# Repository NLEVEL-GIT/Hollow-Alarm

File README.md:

# HollowAlarm

    HollowAlarm was my ship for the Blare Mission of Stardance Hackclub
    HollowAlarm features a simple clock like shape design with 4 keys to control

# Features:

    - 2.25 Inch TFT Display
    - 4 Keys
    - Buzzer... cuz its and alarm

# CAD Model:

    HollowPad is divided in 4 parts.
    - the main shell where eveything connects that include a sorta of cabinet design and dovetail joints to connect to the shell of the alarm.
    - The shell itself consisting of the front piece and back piece to close the clock design

    Everything was in Fusion cuz its lowk fire

# PCB
    It was made in KiCad. Only requiring extra footprints ansd symbols provided by the Blare page!

    The footprints for the Switches are standart MX style Switches!

**Schematic:**

**PCB Layout:**

    Also it has a lot of small silkscreens cuz they lowk cool!

# Firmware Overview
    The firmware can be described as spaghetti code secured by hopes and dreams.
    It gives each button its own function and has a way to swap between 4 background which I made! More can be added by changing the background.h file on the firmware

# BOM:
    Here should be everything you need to make this hackpad

    - 4x Cherry MX Switches
    - 4x DSA Keycaps (or you can make some if u want)
    - 1x Buzzer
    - 1x 2.25" 284x76 TFT Display
    - 1x XIAO ESP32C3
    - 1x Case (4 Printed Parts)

# Extra stuff
    To anyone that is reading the end of this READ ME i wana say thanks for atleast checking out my project.
    With that thanks again and Good Luck on your projects!!!

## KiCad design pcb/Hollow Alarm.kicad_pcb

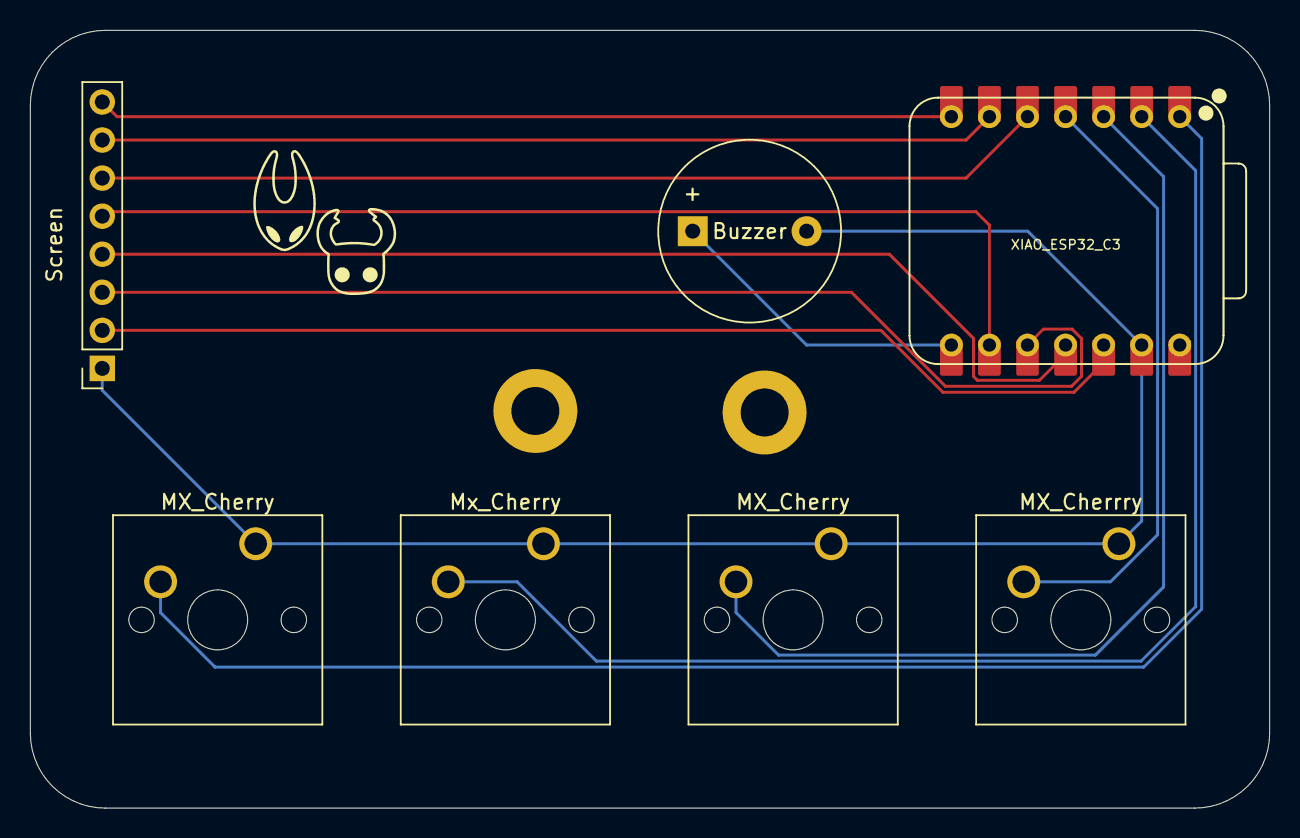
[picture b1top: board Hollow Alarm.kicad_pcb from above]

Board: 2 copper layers, 82.7 x 51.9 mm, 7 parts (0 on the bottom side), 13 nets.

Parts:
Buzzer: Buzzer; Buzzer_12x9.5RM7.6
MX_Cherrry: SW_Push; SW_Cherry_MX_1.00u_PCB
MX_Cherry: SW_Push; SW_Cherry_MX_1.00u_PCB
MX_Cherry#2: SW_Push; SW_Cherry_MX_1.00u_PCB
Mx_Cherry: SW_Push; SW_Cherry_MX_1.00u_PCB
Screen: Conn_01x08_Pin; PinSocket_1x08_P2.54mm_Vertical
XIAO_ESP32_C3: XIAO_ESP32_C3; XIAO-ESP32-C3-DIP

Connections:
GND: Buzzer.2 (-), MX_Cherrry.1, MX_Cherry.1, MX_Cherry#2.1, Mx_Cherry.1, Screen.1, XIAO_ESP32_C3.13 (GND)
unnamed: Buzzer.1 (+), XIAO_ESP32_C3.8 (D7)
unnamed: Screen.3, XIAO_ESP32_C3.10 (D9/BOOT)
unnamed: Screen.4, XIAO_ESP32_C3.11 (D10)
unnamed: Screen.5, XIAO_ESP32_C3.9 (D8)
unnamed: Screen.6, XIAO_ESP32_C3.5 (D4)
unnamed: Screen.7, XIAO_ESP32_C3.6 (D5)
unnamed: Screen.8, XIAO_ESP32_C3.7 (D6)
unnamed: MX_Cherry#2.2, XIAO_ESP32_C3.1 (D0)
unnamed: Mx_Cherry.2, XIAO_ESP32_C3.2 (D1)
unnamed: MX_Cherry.2, XIAO_ESP32_C3.3 (D2)
unnamed: MX_Cherrry.2, XIAO_ESP32_C3.4 (D3)
VCC: Screen.2, XIAO_ESP32_C3.12 (3V3_OUT)
